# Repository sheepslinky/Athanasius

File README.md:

# Athanasius
Creative Delta Robot and 3D printer.

Athanasius is a delta robot with various functions. Many components are derivitive of Athena and other Rep-Raps. Athanasius is refined for increased creative potential which may be of value to artists, designers, and architects, as well as makers and engineers.

Default Firmware is Franklin by Bas Wijnen. It can be run, although not as well, on Marlin. Other firmware, such as smoothie would be possible too.  

Based primarily upon Athena by MTU-MOST.

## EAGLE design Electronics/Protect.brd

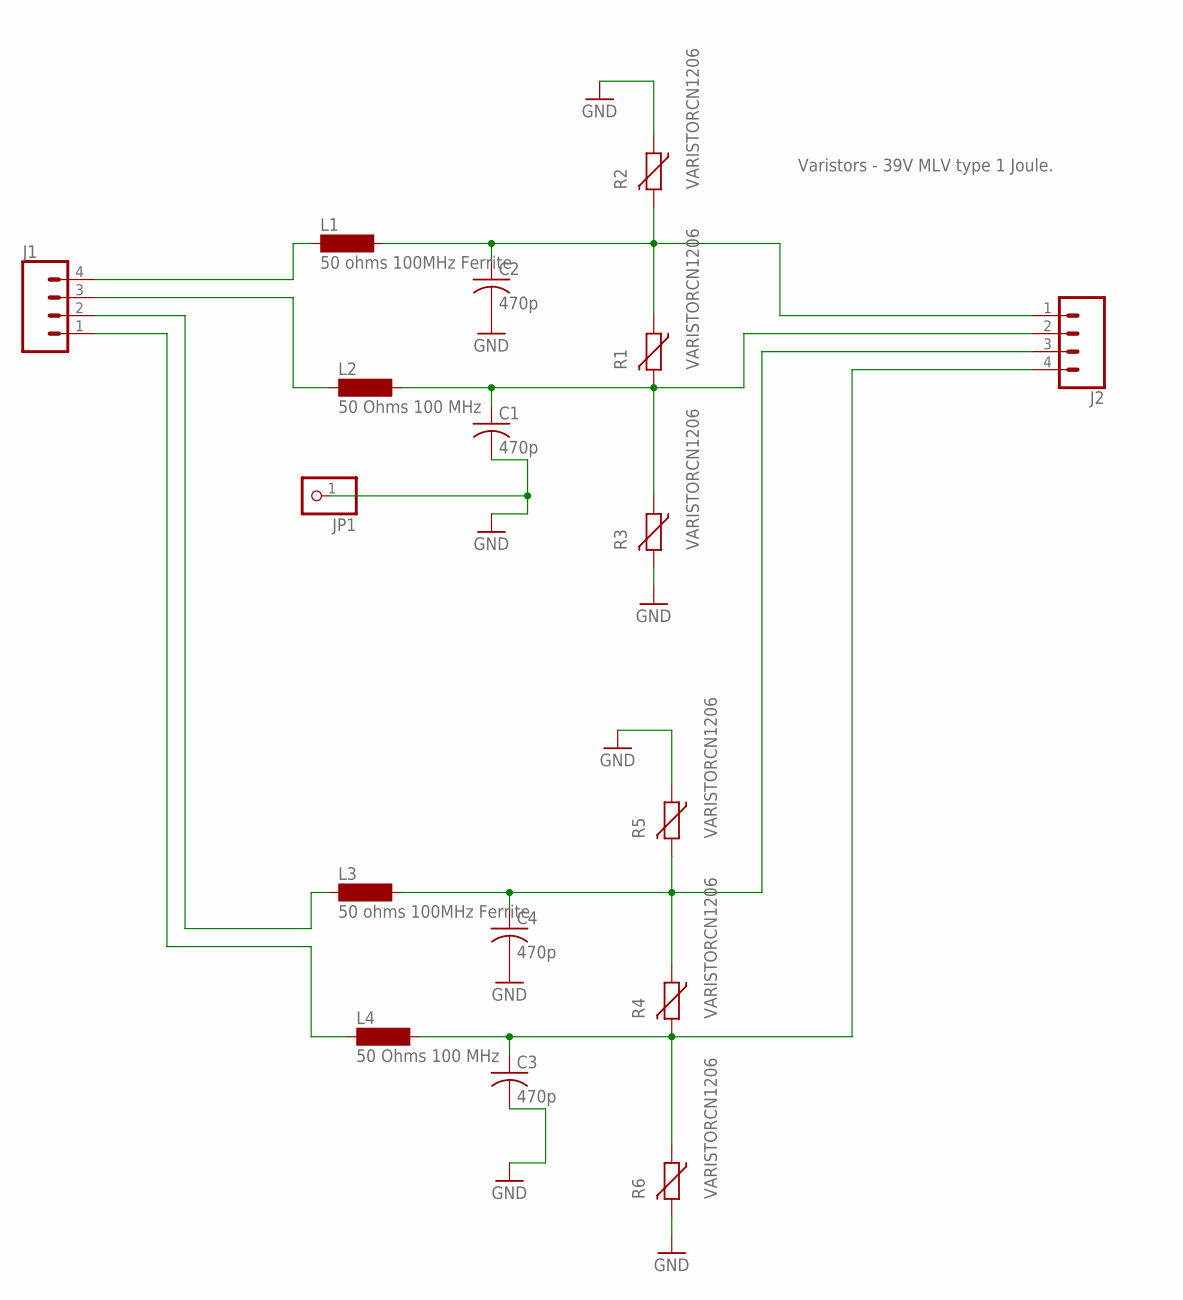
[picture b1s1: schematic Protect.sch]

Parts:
C1, C2, C3, C4: 470p; C0603K
J1, J2: CONN_04; 1X04
JP1: PINHD-1X1; 1X01
L1, L3: 50 ohms 100MHz Ferrite; SM-1206
L2, L4: 50 Ohms 100 MHz; SM-1206
R1, R2, R3, R4, R5, R6: VARISTORCN1206; CT/CN1206

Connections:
GND: C1.2, C2.2, C3.2, C4.2, JP1.1, R2.1, R3.2, R5.1, R6.2
unnamed: C2.1, J2.1, L1.2, R1.1, R2.2
unnamed: J1.4, L1.1
unnamed: C1.1, J2.2, L2.2, R1.2, R3.1
unnamed: J1.3, L2.1
unnamed: C4.1, J2.3, L3.2, R4.1, R5.2
unnamed: C3.1, J2.4, L4.2, R4.2, R6.1
unnamed: J1.2, L3.1
unnamed: J1.1, L4.1

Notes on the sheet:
Varistors - 39V MLV type 1 Joule.

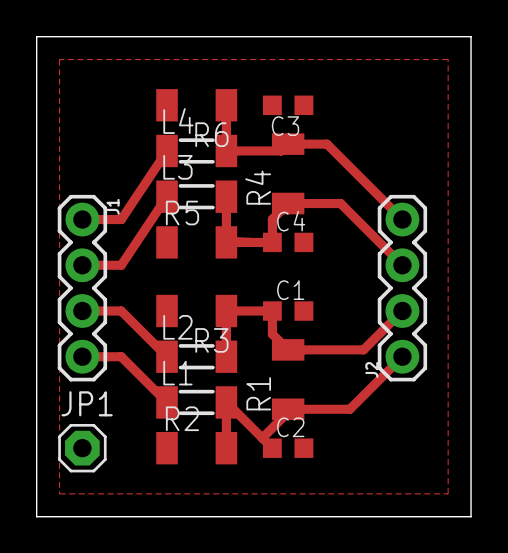
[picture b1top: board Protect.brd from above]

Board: 2 copper layers, 24.1 x 26.7 mm, 17 parts (0 on the bottom side), 9 nets.

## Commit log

2017-10-04 Adding 3D files
2018-03-09 Emi, Back EMF, transient filters

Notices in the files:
parts and their libraries:
SparkFun-Connectors: Licensing: Creative Commons ShareAlike 4.0 International - https://creativecommons.org/licenses/by-sa/4.0
